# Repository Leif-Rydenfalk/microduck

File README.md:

# microduck — a reverse-engineered Pollen Robotics Microduck

*A ce-designs machine (`design:microduck`) and a triad root. Started 2026-09-01.*

Pollen Robotics sells the Microduck (https://pollen-robotics.com/microduck/)
with its firmware and software open source and its **mechanics closed**. This
repo rebuilds the mechanics from everything that is public — the product
photos and video, the published specifications, the open firmware/software
(which encodes joint names, limits, servo IDs and the robot description), and
the open-source lineage it grew from (Open Duck Mini) — as parametric ce-cad
parts that match the images, on the triad shelf, with an evidence ledger.

Leif, 2026-09-01, verbatim: *"Reverse engineer this shit … Because they didn't
open source the mechanics. … It should match the images exactly."*

## What is where

```
README.md            this page
ELECTRONICS-DATASHEET.html  the full electronics datasheet (every IC, the bus, registers, power, pins) with wiring.svg as the graphic
RELEASE.html         THE release dossier — readiness, BOM, files, full step-by-step assembly + wiring (start here)
BUILD-BOOK.html      the build-book overview
ELECTRONICS-DATASHEET.html  the electronics datasheet — `tools/serve.sh` hosts it at localhost:8842
SPEC.md              THE specification we design against — every number sourced
docs/                PARTS.md (every part, one sourced row each) · ELECTRONICS-AND-SOFTWARE.md
                     (boards, bus, IMUs, pins, daemons, wiring diagram) · BOM.md (bought /
                     printed / soft / fasteners, cost vs Pollen $399 and ODM v2 €398) · REBUILD-PROTOCOL.md
                     · PRODUCTION.md (GOAL rung 7: cost per robot at 1/10/100/1000, make/buy and
                     print/mould with break-even, battery shipping + CE/FCC checklist, assembly
                     labour, top-10 unknowns; built from the three lenses in docs/production/ —
                     components.md, process.md, compliance-and-assembly.md)
research/            the dossiers: product page, code mining, images, lineage
images/              reference photos + CATALOG.md (what each shows) + PROPORTIONS.md
spec/                machine-readable spec: specs.json, kinematics.json, bom.json
design.py            the machine — `bin/cad ce-designs/microduck/design.py`
ce-parts/            triad shelf for THIS machine (bought + generated parts)
ce-connections/      connection kinds this machine adds
ce-assemblies/       assembly:microduck and its sub-assemblies (blueprint-first, P12)
out/                 renders, STEP, drawings, release packs — COMMITTED, they are data
tools/               tools written for this project (photo-match, mesh-measure)
firmware/ software/  pointers to the upstream open-source repos + our notes
evidence/            ledger.jsonl + artifacts, append-only
```

This folder is a **triad root**: `CE_TRIAD_ROOT=$PWD ~/dev/ce-workshop/bin/triad check --all`
resolves every `part:` / `connection:` / `assembly:` ref against it first.

## Method

1. **Research** — collect every public fact with its source and quote (research/).
2. **Specify** — SPEC.md: dimensions, DoF, actuators, electronics, materials,
   with confidence per number (published / measured-from-image / inferred).
3. **Blueprint** — `bin/triad-blueprint` boxes for body, head, legs, battery,
   compute, before any part is chosen (PROTOCOLS.md P12).
4. **Design** — one ce-cad part per box, matched against the photos with the
   photo-match tool, checked, rendered, delivered.
5. **Evidence** — every check and comparison lands in the ledger; the machine
   is born T0 and earns its tier.

## Simulated

Pollen's MJCF driven by Pollen's published walking / sit-stand / stand policies
in MuJoCo, with our rebuilt meshes swapped in for every PASSed part (orange).
`out/sim/walk.mp4`, `sitstand.mp4`, `stand.mp4`, `walk_stock.mp4`; every number
in `out/sim/report.md` is measured off the simulation. How to run it in three
commands: `sim/README.md`.

## Status

See `SPEC.md` §Status and `evidence/ledger.jsonl`. Nothing here is a claim
that the design is correct — a number without a source is a defect.

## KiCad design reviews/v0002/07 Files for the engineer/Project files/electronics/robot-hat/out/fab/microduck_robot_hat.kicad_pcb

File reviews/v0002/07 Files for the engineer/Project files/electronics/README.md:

# electronics/ — GOAL.md rung 4: the robot's electronics, known and checked

*Netlist lane, 2026-09-02. The datasheets are on the shelf (ce-parts/, docs/ELECTRONICS-AND-SOFTWARE.md §13); this folder is the robot as one `cecad.netlist.Design`, checked. The Robot HAT as a ce-pcb board is the next lane and lands in `electronics/robot-hat/`.*

## Run it

```
export CE_TRIAD_ROOT="/Users/leifrydenfalk/dev/ce-workshop/ce-designs/microduck:/Users/leifrydenfalk/dev/ce-workshop"
python3 electronics/netlist.py              # exit 0 PASS · 2 FAIL · 3 CANNOT DETERMINE; writes the files below
python3 electronics/netlist.py --self-test  # every check broken on purpose; exit 0 only if every break is caught
```

| file | what |
|---|---|
| `netlist.py` | the Design: host `radxa-zero-3w`, 6 declared bus segments, 25 parts, 28 nets; nine cecad checks + four of its own (`volts/*`, `dxl/ids`, `i2c3/overlay`, `cross/wiring`); the self-test; the report writer |
| `netlist-report.md` | the three-verdict report — every finding in full, with its quote and cite |
| `report.json` | the same findings, machine-readable |
| `netlist.json` | every net and terminal (`cecad.netlist.netlist_json`) — what the HAT board lane `bind()`s to |
| `netlist.graph.json` | the `cecad.graph` document (declaration + derived nets + findings) |
| `firmware.json` | `cecad.netlist.firmware()` — buses, addresses, pins, per-net demand, every null with its reason |
| `elec-spec.json` | a `bin/elec` spec kept as the probe that records ce-elec's refusal (no RK3566 pin roster) |

## The verdict, 2026-09-02 02:20

**FAIL — 75 PASS · 15 FAIL · 28 CANNOT DETERMINE over 118 findings.**

What PASSes (the checks this rung asked for):

- one controller per bus: `i2c3`, `i2c2`, `uart2`, `dxl`, `i2s3`, `csi` — the Radxa, on the vendor's header pins ([brief] p.6 / [wiki])
- I2C3 addresses unique: codec 0x18, BMI088 0x19 + 0x68, ToF 0x29 — and equal to the set Pollen's overlays name (`i2c3/overlay`)
- the 16 Dynamixel IDs unique, inside 0..252, and exactly `JOINT_IDS` + `IMU_DXL_ID` read out of `model.rs` (`dxl/ids`)
- 19 pin identifiers, none on two nets (`gpio`); the host's 5 V and GND joined (`host_power`); every part's signal directions stated (`pin_directions`)
- connectivity agrees pair-for-pair with the rung-5 wiring lane's `wiring/designs/microduck/nets.json` over the 86 terminals both designs know (`cross/wiring`, 3655 pairs)

What FAILs — one thing, fifteen times: **`volts/SERVO_V`**. The runtime declares the servo bus at 6.6–8.2 V (`model.rs:109,113`, read through the servos' own Present Input Voltage) and the XL330-M288-T's band is 3.7–6.0 V ("Input Voltage | 3.7 ~ 6.0 [V] (Recommended : 5.0 [V])", ROBOTIS e-Manual). That is docs §3.4 open question 1 as a verdict: the design as published is over the vendor band. A meter on a production servo's VDD, or Pollen naming a regulated bus or a custom variant, settles it.

What is CANNOT DETERMINE, by name — all of it is the unpublished HAT schematic:

- `power/HAT_3V3`, `power/HAT_1V8`, `volts/HAT_*`: the codec's three domains and the BMI088's two sit on rails nothing on the shelf sources (regulator on the HAT, or the Radxa's 3.3 V — unpublished)
- `current/*` on every rail: the HAT's V5 and SERVO_V provisions carry null capacities (regulator / pass-through unpublished); the XL330 publishes idle and stall but no running current; the pack states no discharge rating
- `volts/SERVO_V imu200.VDD`, `volts/MICBIAS`: the imu_to_dxl board's input band and the mic bias level are unpublished
- `vocabulary/*`: SPK+/SPK−/MIC_IN — audio terminals cecad has no vocabulary for; whether an amplifier sits between codec and speaker is unpublished
- the transceiver behind `dxl/DATA` (ROBOTIS' reference is a 74LVC2G241 with a TX-enable that robotd never drives), the I2S3 mux (M0 asserted; M1 also on the header), MCLK's origin

## What the design file does that the records cannot

1. **Servo IDs.** Fifteen servos share one record, and the ID is an EEPROM register. Each servo is a design-level view of `part:xl330-m288-t` carrying its ID from `model.rs:15-19` as the design's assertion. The self-test puts two servos at ID 10 and the bus check says FAIL.
2. **BMI088.** One package, two I2C targets. cecad reads one address per owner, so the package is wired as `bmi088` (0x19 + supplies) and `bmi088.gyro` (0x68). The self-test moves the gyro to 0x18 and the check names the codec.
3. **HAT pass-throughs.** The HAT record states its header pass-throughs with `bus: I2C/UART`; on the netlist they are copper. Wired with `bus: None` (stated in the file); left as bus terminals they produce a "UART endpoint with no address" that says nothing about the robot — the self-test shows that too.

## Records written by this lane

- `ce-parts/tlv320aic3104/iterations/v0.0.1/electrical.part.json` (+ root symlink) — the codec as a part: three supply domains, I2C 0x18 ("001 1000"), I2S target
- `ce-parts/bmi088/iterations/v0.0.1/electrical.part.json` (+ root symlink) — two I2C targets 0x19/0x68 with the strap inference stated
- `ce-parts/xl330-m288-t/electrical.part.json` — additive: `address_selectable` + `address_basis` on the DATA need (the ID is a register)
- `ce-cad/cecad/netlist.py` `_address_conflict` — **tool fix found by the self-test**: on a bare host (no port standard, nets declared by the design) a duplicate bus address built a FAIL with an empty quote and `Finding` raised `ValueError` instead of reporting. Now quotes the device's own address record and carries the segment's declaration as the assertion. cecad's own `--self-test` output is identical before and after (63 OK; its two pre-existing conformance FAILs are unrelated).

## Tool gaps recorded (P11)

- `cecad/shelf.py` reads one `$CE_PARTS_ROOT`; `netlist.py` builds a symlink union of every `ce-parts` under `$CE_TRIAD_ROOT` in `~/.cache/ce-workshop/shelf-union/<hash>/` and refuses a slug present in two shelves.
- `Design._build_catalogue` admits a shelf record only if it carries `$from: parts.json`; records without it are outside every design's catalogue, which is why the wiring lane's report has no address findings at all. The two records above carry the marker; the servo views are admitted by the design (`_admit`).
- `bin/elec gpio|levels`: REFUSED — `host 'radxa-zero-3w' names no pin_roster`. There is no RK3566 roster in `cecad/data/controllers.json`; the Radxa's pins are the vendor's header table, checked for collisions, never for existence.
- cecad has no vocabulary for audio terminals (speaker, mic) — reported as CANNOT DETERMINE, never passed over.

## Robot HAT as a ce-pcb board

*(next lane — `electronics/robot-hat/board.py`, nets bound from `netlist.json`, DRC → gerbers; this section is its slot.)*

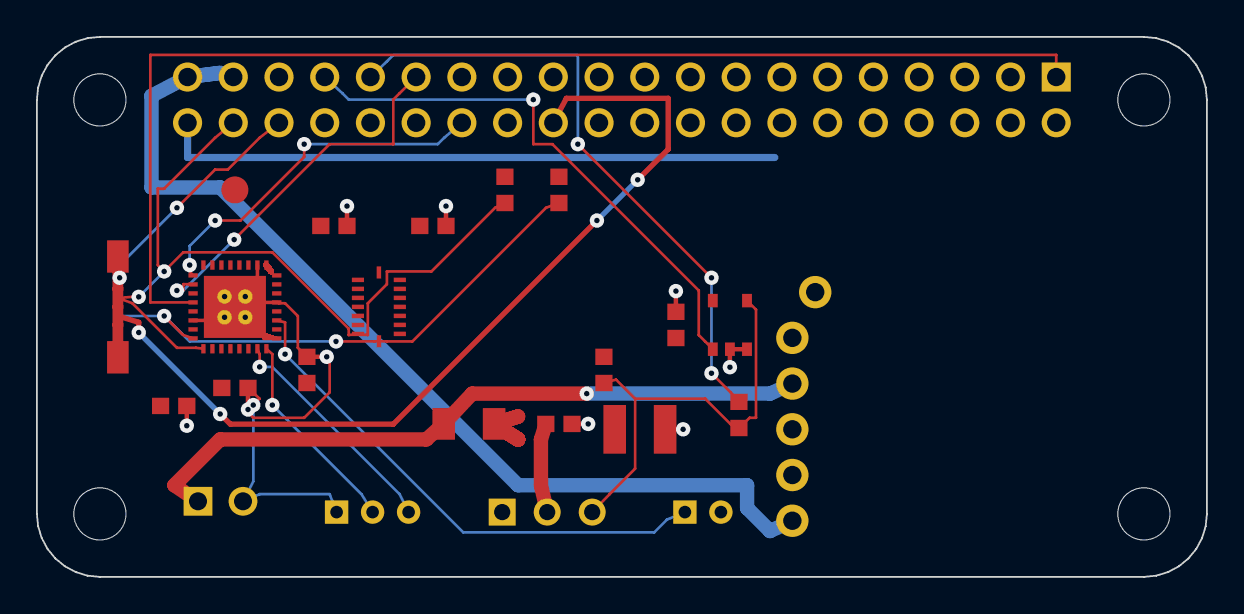
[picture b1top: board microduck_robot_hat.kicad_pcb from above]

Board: 2 copper layers, 65.0 x 30.0 mm, 28 parts (0 on the bottom side), 21 nets.

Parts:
C1: 100n SERVO_V; 0603
C2: bulk (value CANNOT DETERMINE); 1210
C3: 100n U4 VCC; 0603
C4, C5, C6, C7, C8: 100n; 0603
H1, H2, H3, H4: M2.5; mount-M2.5
J1: 40-pin GPIO; header-2x20
J2: VBAT in (B2B-XH-A); jst-b2b-xh-a
J3: DXL bus (B3B-EH-A); jst-b3b-eh-a
J5: Stemma J5 (SM04B-SRSS-TB); jst-sh4-smt-side
J6: speaker (B2B-PH-K-S); jst-b2b-ph-k-s
J7: mic (B3B-PH-K-S); jst-b3b-ph-k-s
R1: 0R link VBAT->SERVO_V; 1206
R2, R12, R13: 10k; 0603
R4: 0R DATA->RX; 0603
TP1: HAT_1V8 (unsourced); test-point
U1: TLV320AIC3104; qfn-32
U2: Pololu D30V30F5; pololu-d30v30f5
U3: BMI088 (dormant); bmi088-lga16
U4: 74LVC1G125; sot753

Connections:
GND: C1.2, C2.2, C3.2, C4.2, C5.2, C6.2, C7.2, C8.2, J1.6, J1.9, J1.14, J1.20, J1.25, J1.30, J1.34, J1.39, J2.2, J3.1, J5.1, J7.1, U1.6, U1.17, U1.21, U1.26, U1.EP, U2.GND1, U2.GND2, U3.2, U3.4, U3.6, U3.10, U3.15, U4.2, U4.3
HAT_1V8: C5.1, TP1.1, U1.32
HAT_3V3: C3.1, C4.1, C6.1, C7.1, C8.1, J1.1, R2.2, R12.2, R13.2, U1.7, U1.18, U1.24, U1.25, U1.31, U3.3, U3.7, U3.11, U3.14, U4.5
J5_3V3: J1.17, J5.2
MICBIAS: J7.3, U1.15
MIC_IN: J7.2, U1.16
SERVO_V: C1.1, C2.1, J3.2, R1.2
SPK_N: J6.2, U1.20
SPK_P: J6.1, U1.19
V5_HAT: J1.2, J1.4, U2.VOUT
VBAT: J2.1, R1.1, U2.VIN
dxl/DATA: J3.3, R2.1, R4.1, U4.4
i2c3/SCL: J1.5, J5.4, R13.1, U1.8, U3.8
i2c3/SDA: J1.3, J5.3, R12.1, U1.9, U3.9
i2s3/BCLK: J1.12, U1.2
i2s3/DIN: J1.40, U1.4
i2s3/DOUT: J1.38, U1.5
i2s3/MCLK: J1.13, U1.1
i2s3/WCLK: J1.35, U1.3
uart2/RX: J1.10, R4.2
uart2/TX: J1.8, U4.1

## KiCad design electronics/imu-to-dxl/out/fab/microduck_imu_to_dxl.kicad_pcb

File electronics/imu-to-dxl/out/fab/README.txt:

Microduck imu_to_dxl v2 (reconstruction)
========================================

40.0 x 22.0 mm, 876.49 mm2, 2 copper layers
stackup   JLCPCB 2-layer 1.6 mm, 1 oz — the commodity default
finish    
rules     JLCPCB 2-layer, standard process — tighter, and single-sourced
parts     24   nets 17   tracks 272   vias 27   drills 38

READ THIS BEFORE ORDERING
-------------------------

1. THE DESIGN RULES WERE CONFIRMED AGAINST THE FAB'S OWN CAPABILITY PAGE.

   Profile: jlcpcb_2l_standard   confirmed 2026-08-20

   CONFIRMED 2026-08-20 against https://jlcpcb.com/capabilities/pcb-capabilities, read that day, for the 2-layer FR-4 1.6 mm 1 oz process. What the page said, verbatim, and what it changed here:
     track / space, 1 oz .... '0.10 / 0.10 mm (4 / 4 mil)'  (2 oz: '0.16 / 0.16 mm (6.5 / 6.5 mil)') -> min_track_mm and min_clearance_mm 0.127 -> 0.10. The old numbers were TIGHTER than the fab, so no board was ever wrongly passed by them.
     plated hole diameter ... '0.15 - 6.3 mm' -> min_via_drill_mm LEFT AT 0.30. The page's floor is the drill the fab owns; over a 1.6 mm board the 8:1 aspect rule on this same profile floors it at 0.20 mm, and 0.30 mm is the size this profile hands the router as a DEFAULT via drill. Lowering it would shrink every via the autorouter places for no gain.
     PTH annular ring, 1 oz . 'Recommended 0.25 mm or above; absolute minimum 0.18 mm' (2 oz: '0.254 mm or above') -> min_annular_ring_mm 0.125 -> 0.25, and min_via_pad_mm 0.55 -> 0.80 (0.30 drill + 2 x 0.25). THIS IS THE CORRECTION THAT MATTERED. The transcribed 0.125 was LOOSER than the fab's own absolute minimum of 0.18, so it passed boards JLCPCB will not build: floorctl rev A had 55 vias at a 0.150 mm ring and a green annular-ring line under it.
     pad hole-to-hole ....... '0.45 mm' -> min_hole_to_hole_mm 0.50 -> 0.45.
     routed edge clearance .. '>= 0.2 mm' -> min_edge_clearance_mm 0.30 -> 0.20.
     maximum board size ..... '670 x 600 mm'.
     outer copper ........... '1 oz / 2 oz / 2.5 oz / 3.5 oz / 4.5 oz'.
     surface finish ......... 'HASL (leaded / lead-free), ENIG, OSP'.
   STILL TRANSCRIBED, NOT ON THAT PAGE: min_hole_to_copper_mm, min_silk_width_mm, min_silk_height_mm, min_silk_to_pad_mm, min_mask_sliver_mm, min_text_to_edge_mm and max_aspect_ratio. Each says so in its own statement. Confirm those against JLCPCB's silkscreen and solder-mask notes before relying on one of them alone.
   MULTILAYER (4-layer), read off the same page the same day and NOT the rules in this profile — this profile is the 2-LAYER process and a board built on it that goes out as 4-layer must be re-read against these: outer track/space '0.10 / 0.10 mm (4 / 4 mil)', inner track/space '0.09 / 0.09 mm (3.5 / 3.5 mil)', inner copper '0.5 oz / 1 oz / 2 oz' with '0.5oz by default', plated hole '0.15 - 6.3 mm', and PTH annular ring at 1 oz 'Recommended 0.20 mm or above; absolute minimum 0.15 mm' — LOOSER than the 2-layer 0.25 / 0.18, so a via that clears the 2-layer rule clears the 4-layer one.

   A capability page changes. Re-read it if this date is old.

3. PACKAGE DIMENSIONS ARE TRANSCRIBED, NOT MEASURED.

   NOT ONE DIMENSION IN THIS FILE WAS MEASURED FROM A PART IN SOMEBODY'S HAND. They are transcriptions of published outlines. That is a much stronger position than cecad/data/atech_footprint.json (which is authored from nothing), and a much weaker one than a micrometer. Before a board is ORDERED, the footprint of every part whose confidence is not `standard` must be checked against the datasheet of the exact orderable part number — `pcbcheck.check_footprints()` prints that list and refuses to go quiet about it.

4. WHAT THE DESIGN RULE CHECK DID NOT CHECK.

   Signal integrity, impedance, return paths, EMC, thermal design beyond a
   bare-trace current figure, and whether the circuit works at all. A board
   that passes DRC is a board that can be MANUFACTURED.

DRC RESULT
----------

   verdict: FAIL
   36 pass, 3 fail, 3 cannot determine

   [FAIL] unrouted GND
   [FAIL] unrouted IMU_INT1
   [FAIL] unrouted V3V3
   [CANNOT DETERMINE] binding microduck_imu_to_dxl
   [CANNOT DETERMINE] current microduck_imu_to_dxl
   [CANNOT DETERMINE] via microduck_imu_to_dxl

FILES
-----
   microduck_imu_to_dxl-F.Cu.GTL
   microduck_imu_to_dxl-B.Cu.GBL
   microduck_imu_to_dxl-F.Mask.GTS
   microduck_imu_to_dxl-B.Mask.GBS
   microduck_imu_to_dxl-F.Silk.GTO
   microduck_imu_to_dxl-B.Silk.GBO
   microduck_imu_to_dxl-F.Paste.GTP
   microduck_imu_to_dxl-B.Paste.GBP
   microduck_imu_to_dxl-Edge.Cuts.GKO
   microduck_imu_to_dxl-PTH.drl
   microduck_imu_to_dxl-NPTH.drl
   microduck_imu_to_dxl-positions.csv
   microduck_imu_to_dxl-bom.csv
   microduck_imu_to_dxl.kicad_pcb

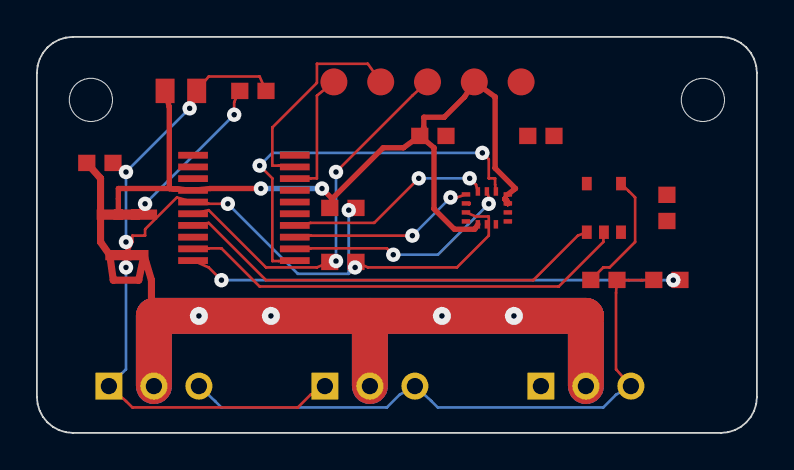
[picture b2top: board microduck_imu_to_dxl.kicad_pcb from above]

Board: 2 copper layers, 40.0 x 22.0 mm, 24 parts (0 on the bottom side), 17 nets.

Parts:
C1: 1u CIN; 0603
C2: 4u7 COUT; 0805
C3: 10n BYPASS; 0603
C4, C5, C6, C7: 100n; 0603
C8: 100n NRST; 0603
H1, H2: M2; mount-M2
J1, J2, J3: DXL bus (B3B-EH-A); jst-b3b-eh-a
R1: 0R DXL_DATA->U3.Y; 0603
R2: 0R DXL_DATA->RX; 0603
TP1: SWDIO; test-point
TP2: SWCLK; test-point
TP3: NRST; test-point
TP4: 3V3; test-point
TP5: GND; test-point
U1: LSM6DSV16X; lga-14l-2p5x3
U2: STM32G031F6P6; tssop-20
U3: 74LVC1G125; sot753
U4: LP2985A-33DBVR; sot-23-5

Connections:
BYPASS: C3.1, U4.4
DIR: U2.7, U3.1
DXL_DRV: R1.1, U3.4
GND: C1.2, C2.2, C3.2, C4.2, C5.2, C6.2, C7.2, C8.2, J1.1, J2.1, J3.1, TP5.1, U1.2, U1.3, U1.6, U1.7, U2.5, U3.3, U4.2
IMU_INT1: U1.4, U2.8
MCU_RX: R2.2, U2.10
MCU_TX: U2.9, U3.2
NRST: C8.1, TP3.1, U2.6
SERVO_V: C1.1, J1.2, J2.2, J3.2, U4.1, U4.3
SPI_MISO: U1.1, U2.13
SPI_MOSI: U1.14, U2.14
SPI_NSS: U1.12, U2.11
SPI_SCK: U1.13, U2.12
SWCLK: TP2.1, U2.19
SWDIO: TP1.1, U2.18
V3V3: C2.1, C4.1, C5.1, C6.1, C7.1, TP4.1, U1.5, U1.8, U1.10, U1.11, U2.4, U3.5, U4.5
dxl/DATA: J1.3, J2.3, J3.3, R1.2, R2.1

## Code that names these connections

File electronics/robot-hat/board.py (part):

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      low through the buffer, TX high (idle) releases it to the 10 k pull-up.
      RX reads the line through R4 (0R). This TOPOLOGY is our proposal; the
      fitted transceiver stays CANNOT DETERMINE.
  D4  3.3 V rails: HAT_3V3 from 40-pin pin 1 and J5_3V3 from pin 17 — both
      '+3.3V' per [brief] p.6 / part:radxa-zero-3w header_40pin. Whether the
      real HAT does this or regulates its own: CANNOT DETERMINE.
  D5  1.8 V: NOT SOLVED, and now known to be UNSOLVABLE FROM THE HEADER. The
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# 18 DRVDD, 19 HPLOUT, 20 HPLCOM, 21 DRVSS, 22 HPRCOM, 23 HPROUT, 24 DRVDD,
# 25 AVDD, 26 AVSS2, 27 LEFT_LOP, 28 LEFT_LOM, 29 RIGHT_LOP, 30 RIGHT_LOM,
# 31 RESET, 32 DVDD. 'NOTE: Connect device thermal pad to DRVSS.'
AIC_PINS = {"MCLK": "1", "BCLK": "2", "WCLK": "3", "DIN": "4", "DOUT": "5",
            "GND": "6", "IOVDD": "7", "SCL": "8", "SDA": "9",
            "AVDD": "25", "DVDD": "32"}

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    b.attach("HAT_3V3", "U1.18")             # DRVDD — one band with AVDD, §8.3
    b.attach("HAT_3V3", "U1.24")             # DRVDD
    b.attach("MICBIAS", "U1.15")             # 'MICBIAS | 15 | O'
    b.attach("MIC_IN", "U1.16")              # D6: MIC2R/LINE2R, pin 16
    b.attach("SPK_P", "U1.19")               # D6: HPLOUT
    b.attach("SPK_N", "U1.20")               # D6: HPLCOM
    b.attach("HAT_1V8", "TP1.1")             # D5 — see the header table above
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        rep = check(b, verbose=verbose)
        return b, rep
    # Two hand-laid spines, claimed before the router runs:
    #  - HAT_3V3 rides B.Cu from J1 pin 1 (a through-hole pad reaches the
    #    back layer through its own barrel) along y=23.3, under the corridor
    #    south of the header, so eighteen 3.3 V joins become short hops.
    #    One deliberate cost: it slices the eventual GND pour along that
    #    line; the pour reconnects around x>41 — checked on the bottom plot.
    #  - i2s3/DIN goes the long way: J1 pin 38 escapes upward into the lane
    #    between the header's outer row and the board edge, west along
    #    y=29.0, down the west flank of the header, then to codec DIN
    #    (pin 4). The router failed this join twice ('no legal path');
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                        (41.0, 23.3)], width=0.4, layer="B.Cu")
    # MEASURED DEFECT, fixed 2026-09-02 (lane D): this spine used to start at
    # J1 pad 38 while carrying net i2s3/DIN. Pad 38 is I2S3_SDI = i2s3/DOUT
    # (see `pins` above); the DIN pad is 40. The DRC caught it as three
    # 0.000 mm clearance failures — 'track i2s3/DIN on F.Cu / pad J1.38' plus
    # two codec pads the old diagonal approach cut across (U1.2 BCLK, U1.3
    # WCLK). The track now leaves the RIGHT pad and comes into the codec's
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    # own budget, HAT_3V3 the largest.
    b.autoroute(nets=["HAT_3V3"], width=0.3, effort=22, via_cost=4.0,
                verbose=verbose)
    b.autoroute(nets=["J5_3V3", "HAT_1V8"], width=0.3, effort=10,
                via_cost=4.0, verbose=verbose)
    b.autoroute(nets=["GND"], effort=15, via_cost=3.0, verbose=verbose)
    b.pour("GND", "B.Cu")
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
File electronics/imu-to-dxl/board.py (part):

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
# LP2985A-33DBVR, TI SLVS522S (JULY 2004 - REVISED MAY 2025), Figure 4-1
# 'DBV Package, 5-Pin SOT-23 (Top View)' + Table 4-1 Pin Functions p.3/33:
# 1 VIN, 2 GND, 3 ON/OFF ('Tie this pin to VIN if unused'), 4 BYPASS,
# 5 VOUT. Recommended Operating Conditions p.4: VIN 2.5..16 V, IOUT 0..150 mA,
# CIN >= 1 uF, COUT >= 2.2 uF nominal (>1 uF effective).
LDO_CITE = ("TI SLVS522S (rev. May 2025) Figure 4-1 + Table 4-1, p.3/33: "
            "1 VIN, 2 GND, 3 ON/OFF, 4 BYPASS, 5 VOUT in the DBV 5-pin "
            "SOT-23; Recommended Operating Conditions p.4 VIN 2.5-16 V, "
            "IOUT <= 150 mA, CIN >= 1 uF, COUT >= 2.2 uF")

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    # -- E3: the 3.3 V rail --------------------------------------------------
    b.attach("SERVO_V", "U4.1")            # VIN
    b.attach("GND", "U4.2")
    b.attach("SERVO_V", "U4.3")            # ON/OFF — 'Tie this pin to VIN if unused'
    b.net("V3V3", "U4.5")
    b.attach("BYPASS", "U4.4")
    b.attach("SERVO_V", "C1.1"); b.attach("GND", "C1.2")
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    b.attach("MCU_RX", "R2.2")

    # -- E4/E6: the IMU ------------------------------------------------------
    b.attach("V3V3", f"U1.{IMU_PINS['VDD']}")
    b.attach("V3V3", f"U1.{IMU_PINS['VDDIO']}")
    b.attach("GND", f"U1.{IMU_PINS['GND']}")
    b.attach("GND", "U1.7")
    b.attach("SPI_NSS", f"U1.{IMU_PINS['CS']}")
    b.attach("SPI_SCK", f"U1.{IMU_PINS['SCK']}")
    b.attach("SPI_MOSI", f"U1.{IMU_PINS['SDI']}")
    b.attach("SPI_MISO", f"U1.{IMU_PINS['SDO']}")
    b.attach("IMU_INT1", f"U1.{IMU_PINS['INT1']}")
    b.attach("GND", "U1.2")                # E6 — AH1/Qvar1 disabled
    b.attach("GND", "U1.3")                # E6 — AH2/Qvar2 disabled
    b.attach("V3V3", "U1.10")              # E6 — OCS_Aux to Vdd_IO
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    spine = [_p("J1", "2"), (6.5, 6.5), (30.5, 6.5), _p("J3", "2")]
    branch = [(18.5, 6.5), _p("J2", "2")]
    for layer in ("F.Cu", "B.Cu"):
        b.track("SERVO_V", spine, width=POWER_W, layer=layer)
        b.track("SERVO_V", branch, width=POWER_W, layer=layer)
    # Stitching vias tie the two runs together along the horizontal lane.
    for x in (9.0, 13.0, 22.5, 26.5):
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    # 13 pads needs at least 12 passes. V3V3 has 13 (measured), so effort 8
    # left it in 9 islands on the first run — that is the number this budget
    # is set from, not a guess.
    # SERVO_V's THREE CONNECTOR PINS are already joined by the comb above.
    # What is left of that net is the LDO branch — U4.1 (VIN), U4.3 (ON/OFF,
    # tied to VIN) and C1.1 — which carries this board's own milliamps, not
    # the pass-through, so the router draws it at 0.400 mm and that is the
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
